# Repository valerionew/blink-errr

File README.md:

# BLINK-ERRR  
*For how long this lady will be able to blink her eye on a CR2032 cell?*  
**We'll see!**

<!-- TOC depthFrom:2 depthTo:6 withLinks:1 updateOnSave:1 orderedList:0 -->

- [Purpose of the project](#purpose-of-the-project)
- [Artwork](#artwork)
- [Hardware](#hardware)
- [Firmware](#firmware)
	- [Toolchain and environment setup](#toolchain-and-environment-setup)
	- [Programmers](#programmers)
	- [Uploading with jtag2updi and avrdude (AVRDUDESS)](#uploading-with-jtag2updi-and-avrdude-avrdudess)
	- [Firmware working and internals](#firmware-working-and-internals)
		- [v1.0](#v10)
		- [v1.1](#v11)
- [Battery life expectancy](#battery-life-expectancy)

<!-- /TOC -->

## Purpose of the project
_This project may or may not have any sense in the traditional sense of having a sense._ The project is the product of some experimentation that lay between a **purely technical challenge** and **an artistic dimension**.

I got intrested in low power microcontroller stuff, and I wanted to do a simple little project to see for how long I could blink an led on a small battery, optimizing as much as I could. The specs i challenged myself to comply with were pretty easy:

- Blink an LED every 3-10 seconds;
- The blink should be at least visible outside without direct sunlight;
- The blink should be produced by a microcontroller;
- It should run as long as possible on a single CR2032 (obviously without removing power to the microcontroller);
- It should be the size and shape of a coin or little more.

In this form it remained for a long time just an idea in my drawer, until I found a nice way to express it to a non-technical audience. That was the point where i conceived BLINK-ERRR as we know it.  

## Artwork
While the concept for this project is mine, the artwork on the front of the board is a kind gift, courtesy of Francesca Ravasio. Kudos to her!

## Hardware
The hardware is based around an **ATtiny202**, one of the newest *(2018)* microcontroller in the ATtiny family. This microcontroller offers great low power performances, with the ability to run on the 32kHz oscillator and a **0.1uA** power down mode.  

 The original plan was to light the led with a square wave generated by the microcontroller, filtered through an LC lowpass passive filter, to not waste any power across a liming resistor. In the end, the square wave solution did not bring any advantage, so **the filter was removed and L1 was replaced with a resistor**.  

 R1 is the placeholder for a shunt, replaced with a 0 ohm jumper link in the final version.

## Firmware

### Toolchain and environment setup
I'm using MPLAB X with the AVR GCC toolchain installed.  
Installing the toolchain might be trivial if you have experience with MPLAB X, if not just follow these steps (for Windows):
- Download the avr GCC toolchain from Microchip [here](https://www.microchip.com/mplab/avr-support/avr-and-arm-toolchains-c-compilers).
- Extract the toolchain to a know path in your system. I've used `C:\Program Files (x86)\Microchip\avr-gcc`
- Open MPLAB X and go to Tools -> Options -> Embedded -> Build Tools -> Add...
- Select **the bin folder** in your avr-gcc folder.  

Now your toolchain should be set up.

### Programmers
The ATtiny202 uses the new UPDI inteface, for which i didn't have any programmer. There are a lot of options:
- **[jtag2updi](https://github.com/ElTangas/jtag2updi) (DIY / Arduino based)**: this is the DIY solution, you can upload this code to an Arduino Uno and use it as a programmer. This is the approach i've used. I'm not sure if this interface can be used for hardware debugging.
- **[MPLAB Snap](https://www.microchip.com/developmenttools/ProductDetails/PartNO/PG164100) (Cheapest official programmer)**: This is a new line of very cheap programmers by Microchip. It is very cheap but, beeing new, it has not a lot of support yet. There's little or no support for debugging.
- **[Atmel-ICE](https://www.microchip.com/DevelopmentTools/ProductDetails/ATATMEL-ICE) (Programmer and debugger)**: This is the traditional AVR programmer from Atmel. It's the most expensive in this list (about 120€), but it is also an hardware debugger.
- **[PICKit4](https://www.microchip.com/developmenttools/ProductDetails/PG164140) (Most universal)**: Probably the most universal programmer of all of these. It supports both AVR and PICS. It would be probably a better choice over the Atmel ICE, but i'm not sure of the PICKit hardware debug capabilities.
### Uploading with jtag2updi and avrdude (AVRDUDESS)
As stated above, i've used the jtag2updi solution. The Author has provided a modified `avrdude.conf` file that can be passed to avrdude to add the support for the programmer and the UPDI compatible targets.  

I've uploaded it to an Arduino Uno using the Arduino IDE.
Contrary to what the author states, in my case **there was no need to cut or disable the auto-reset feature**, it works fine as is. I've connected the target to pin 6 of the Arduino and powered it with 5V from the Arduino board. The target mcu is connected to the arduino through three cables soldered directly on the pins going into the Arduino headers.  

I've used avrdude in the form of [AVRDUDESS by Zak Kemble](http://blog.zakkemble.net/avrdudess-a-gui-for-avrdude/), a GUI for avrdude. You need to install it and replace the `avrdude.conf` file in the installation folder with the one found in the jtag2updi repo.

The final command line generated by AVRDUDESS is nothing out of the ordinary, but it's reported here for reference:  
`-c jtag2updi -p t202 -P COM16 -b 115200 -U flash:w:"[replace with firmware location]":a `

### Firmware working and internals

#### v1.0
The v1.0 version of the firmware relies on the **watchdog timer** to reset the microcontroller every period.  
The firmware is **very simple and organized in functions** to stress the functional role of each code section.  
The flow can be schematized as following:
1. **First power up**
1. **Set the led as output**
1. **Initialize the system**
 	* Set the CPU clock to 1kHz
	* Enable and setup the watchdog to reset the microcontroller in 8 seconds
1. **Enter the infinite loop**
	* Blink the LED
	* Go to sleep (*power-down mode*) and wait for the watchdog reset, then restart from step 1  

This microcontroller **doesn't have the watchdog interrupt**, so the firmware had to rely on the resets.  
This has proven to be a **very inefficient method** to periodically reset the microcontroller, since the reset takes about 60 milliseconds during which the uC consumes a lot of power (for reference, the actual code execution takes about 1 ms).  
The `while(1)` loop is pointless in this application, and was kept just for future use.

#### v1.1
The v1.1 version of the firmware addresses the inefficiency of the v1.0, switching from the watchdog timer to the **Periodic Interrupt Timer** function in the **Real Time Counter** peripheral.  
The flow can be schematized as following:
1. **First power up**
1. **Set the led as output**
1. **Initialize the system**
 	* Set the CPU clock to 1kHz
	* Enable and setup the RTC to run on the 32kHz oscillator prescaled to 1kHz. Then set the PIT to happen every in 8 seconds, and enable the PIT interrupts.
1. **Enter the infinite loop**
	* Blink the LED
	* Go to sleep (*power-down mode*) and wait for the PIT wakeup
	* Clear the PIT flag and restart the loop

This is the **only other wake-up source from power down mode**, and it's likely that this was the proper method to do what i did in v1.0.  
On older AVRs it was done as in my v1.0, with the difference that the watchdog could just generate an interrupt instead of resetting the whole chip. In newer AVRs the watchdog interrupt functionality was probably deprecated by **the introduction of the RTC peripheral with its PIT capability**.

For reference, this is the current consumption for every cycle (with a 1kohm shunt), with the v1.0 waveform in blue and the v1.1 waveform in yellow:

The tall and skinny spike is the actual code exectuion and blink, and **the blue big rectangle is the extra consumption from the reset**.

*The v1.1 seems to consume a lot more in sleep, but according to my measures in DC it looks like this is not the case, and it's just a weird artifact of the waveform save function of my oscilloscope*

## Battery life expectancy
From my measures the blink phase consumes 1mA and lasts about 12ms. This phase is followed by the sleep phase consumption, lasting about 8s, with the consumption varying upon battery voltage: 2uA at highest voltage, dropping to 0.7uA at the lowest voltage. Making a conservative estimation, we can say it is always 2uA.

We can say that we want to transform the red area in the picture, into the blue one, to get the average consumption per period *T*, which coincides con the average consumption per unit of time, because it's constant.   
The red area is 1mA * 12ms = **12uC** (the result is in coulomb because 1A = 1C/1s). We can now obtain the height of the blue area: 12uC/8s = **1.5uA**.  
So, **the equivalent current draw is 3.5uA**.

**For a 200mA CR2032, we can expect the system to run for about 6 years, with this figure beeing a conservative estimate**. Realistically, we won't expect it to run any longer, because of component aging and the battery getting close to the end of it's shelf life.

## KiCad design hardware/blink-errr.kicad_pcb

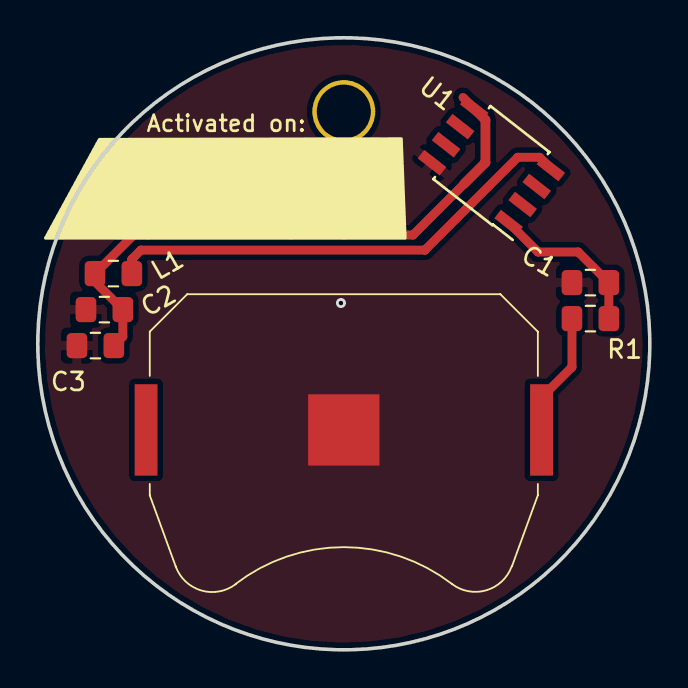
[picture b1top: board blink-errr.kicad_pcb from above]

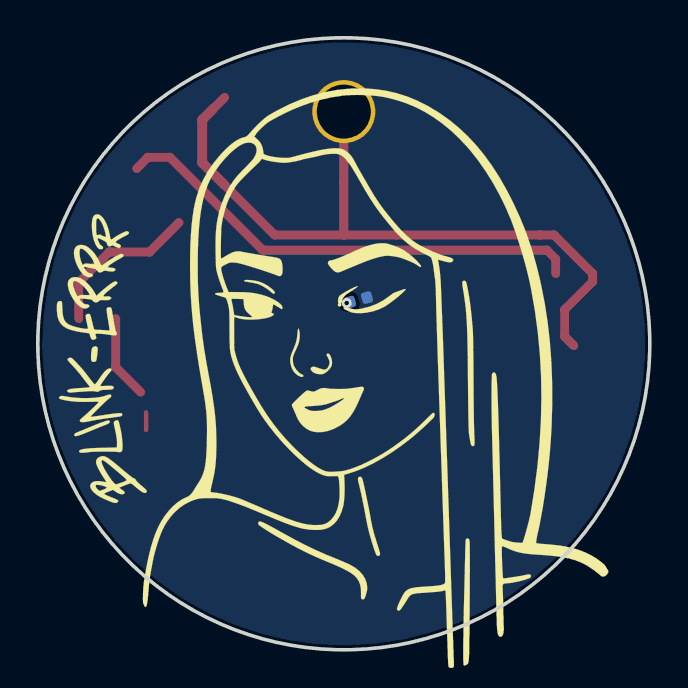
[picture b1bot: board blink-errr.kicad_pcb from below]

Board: 2 copper layers, 34.0 x 34.0 mm, 9 parts (2 on the bottom side), 5 nets.

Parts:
BT1: Battery_Cell; BatteryHolder_Keystone_3034_1x20mm
C1, C2, C3: C; C_0805_2012Metric_Pad1.15x1.40mm_HandSolder
D1: LED; LED_0402_1005Metric
H1: MountingHole; MountingHole_3.2mm_M3_DIN965_Pad
L1: L; L_0805_2012Metric_Pad1.15x1.40mm_HandSolder
R1: R; R_0805_2012Metric_Pad1.15x1.40mm_HandSolder
U1: ATtiny202-SS; SOIC-8_3.9x4.9mm_P1.27mm

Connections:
FEEDBACK: C2.1, C3.1, D1.2, H1.1, L1.2, U1.5
GND: BT1.2, C1.2, C2.2, C3.2, D1.1, U1.8
unnamed: BT1.1, R1.2
unnamed: L1.1, U1.4
VCC: C1.1, R1.1, U1.1

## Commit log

2019-03-25 updated gitignore
2019-03-25 added gitattributes
2019-03-25 ignoring disasm ouptut
2019-03-25 hardware files updates
2019-03-25 Preparing for readme update
2019-03-25 First draft of the readme
2019-03-25 readme fix
2019-03-26 Added informations to the readme
2019-03-26 update gitignore
2019-03-26 added files because of a gitignore bug
2019-03-26 corrected register names
2019-03-26 fixing typos
2019-03-26 removed spaces
2019-03-29 Added uploader folder exception in gitignore
2019-03-30 IDE's project update, no changes to the code
2019-03-30 Added firmware section in readme
2019-03-30 Firmware v1
2019-03-30 Added TOC + minor corrections to the readme
2019-03-30 readme updates
2019-04-01 Comments on the code
2019-04-04 firmware cleanup
2019-04-20 New firmware! Using the PIT timer instead of the watchdog reset
2019-04-20 Added current measurement between firmwares
2019-04-22 Create FIRMWARE_LICENSE
2019-04-22 Revert "Create FIRMWARE_LICENSE"
    This reverts commit 8d0677ea95b4583287524c6d43a134a521c53847.
2019-04-22 Added correct firmware license
2019-04-22 Firmware v1.1
2019-04-22 Added v1.1 explaination to the readme
2019-04-22 Added battery life expectancy explaination
2019-10-03 Typo in readme
2020-06-20 update link
